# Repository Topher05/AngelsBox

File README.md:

# AngelsBox Leverless Controller

A custom-designed leverless controller for fighting games, inspired by the Flatbox project. This project includes PCB designs created in KiCad and 3D models designed in Fusion 360. Keyboard part footprints from external repositories are utilized for precision and compatibility.

## Features

- **Custom PCB Design**: Designed using KiCad, tailored for leverless controller configurations.
- **3D Models**: Created in Fusion 360 for the case and structural components.
- **Keyboard Compatibility**: Leveraging community-driven footprints for key switches and other keyboard-related parts.
- **Fighting Game Optimized**: Designed with ergonomics and precision in mind for competitive play.
- **Firmware**: Uses [GP2040-CE](https://gp2040-ce.info/web-configurator/) for firmware configuration and setup.

## Contents

1. **PCB Design**:
   - KiCad project files for the controller PCB.
   - Schematic and layout files.
   - Gerber files ready for manufacturing.

2. **3D Models**:
   - Fusion 360 files and exported STL models.
   - Case and structural parts for assembly.

3. **Documentation**:
   - Build instructions and assembly tips.
   - Information about external repositories used for keyboard footprints.

## Requirements

- **KiCad**: For viewing and editing PCB design files.
- **Fusion 360**: For modifying or inspecting the 3D models.
- **3D Printer**: To print the case and other structural parts.
- **PCB Manufacturer**: To fabricate the PCB using the provided Gerber files.
- **Firmware Configurator**: Access [GP2040-CE Web Configurator](https://gp2040-ce.info/web-configurator/) for firmware setup.

## Setup and Assembly

1. **PCB Fabrication**:
   - Send the provided Gerber files to your preferred PCB manufacturer.

2. **3D Printing**:
   - Print the STL files using a 3D printer.
   - Ensure proper filament material based on desired durability and aesthetics.

3. **Assembly**:
   - Solder components onto the fabricated PCB.
   - Assemble the 3D-printed case and secure the PCB inside.
   - Install key switches and other hardware components.

4. **Firmware Configuration**:
   - Use the [GP2040-CE Web Configurator](https://gp2040-ce.info/web-configurator/) to configure the firmware for your controller.

5. **Testing**:
   - Connect the controller to a compatible device.
   - Verify inputs and functionality through fighting game or test software.

## Contributions

This project is open for contributions! If you have improvements or suggestions, feel free to submit pull requests or create issues.

## Acknowledgments

- Thanks to the creators of the Flatbox project for inspiration.
- Gratitude to the contributors of open-source keyboard footprint repositories.

## License

This project is licensed under [MIT License](LICENSE).

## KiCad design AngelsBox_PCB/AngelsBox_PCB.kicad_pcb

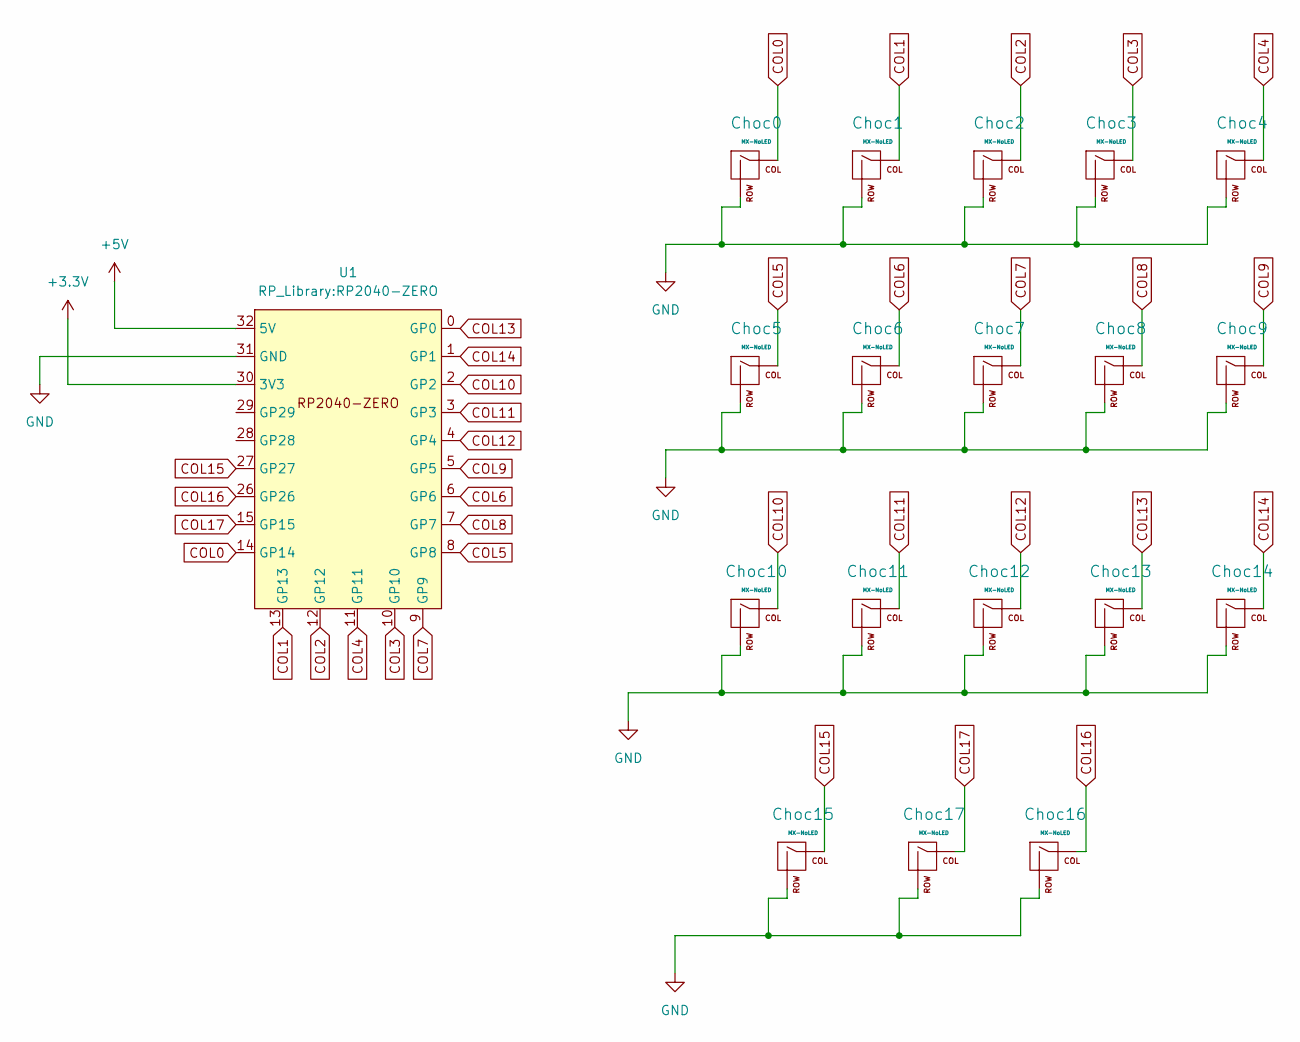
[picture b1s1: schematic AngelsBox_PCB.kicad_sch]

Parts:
Choc0, Choc1, Choc2, Choc3, Choc4, Choc5, Choc6, Choc7, Choc8, Choc9, Choc10, Choc11, Choc12, Choc13, Choc14: MX-NoLED; Kailh_Choc_Hotswap-CircleDesign
Choc15, Choc16, Choc17: MX-NoLED; KailhChoc-1U-Hotswap
U1: RP2040-ZERO

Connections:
+3.3V: U1.30 (3V3)
+5V: U1.32 (5V)
COL0: Choc0.1 (COL), U1.14 (GP14)
COL1: Choc1.1 (COL), U1.13 (GP13)
COL2: Choc2.1 (COL), U1.12 (GP12)
COL3: Choc3.1 (COL), U1.10 (GP10)
COL4: Choc4.1 (COL), U1.11 (GP11)
COL5: Choc5.1 (COL), U1.8 (GP8)
COL6: Choc6.1 (COL), U1.6 (GP6)
COL7: Choc7.1 (COL), U1.9 (GP9)
COL8: Choc8.1 (COL), U1.7 (GP7)
COL9: Choc9.1 (COL), U1.5 (GP5)
COL10: Choc10.1 (COL), U1.2 (GP2)
COL11: Choc11.1 (COL), U1.3 (GP3)
COL12: Choc12.1 (COL), U1.4 (GP4)
COL13: Choc13.1 (COL), U1.0 (GP0)
COL14: Choc14.1 (COL), U1.1 (GP1)
COL15: Choc15.1 (COL), U1.27 (GP27)
COL16: Choc16.1 (COL), U1.26 (GP26)
COL17: Choc17.1 (COL), U1.15 (GP15)
GND: Choc0.2 (ROW), Choc1.2 (ROW), Choc2.2 (ROW), Choc3.2 (ROW), Choc4.2 (ROW), Choc5.2 (ROW), Choc6.2 (ROW), Choc7.2 (ROW), Choc8.2 (ROW), Choc9.2 (ROW), Choc10.2 (ROW), Choc11.2 (ROW), Choc12.2 (ROW), Choc13.2 (ROW), Choc14.2 (ROW), Choc15.2 (ROW), Choc16.2 (ROW), Choc17.2 (ROW), U1.31 (GND)

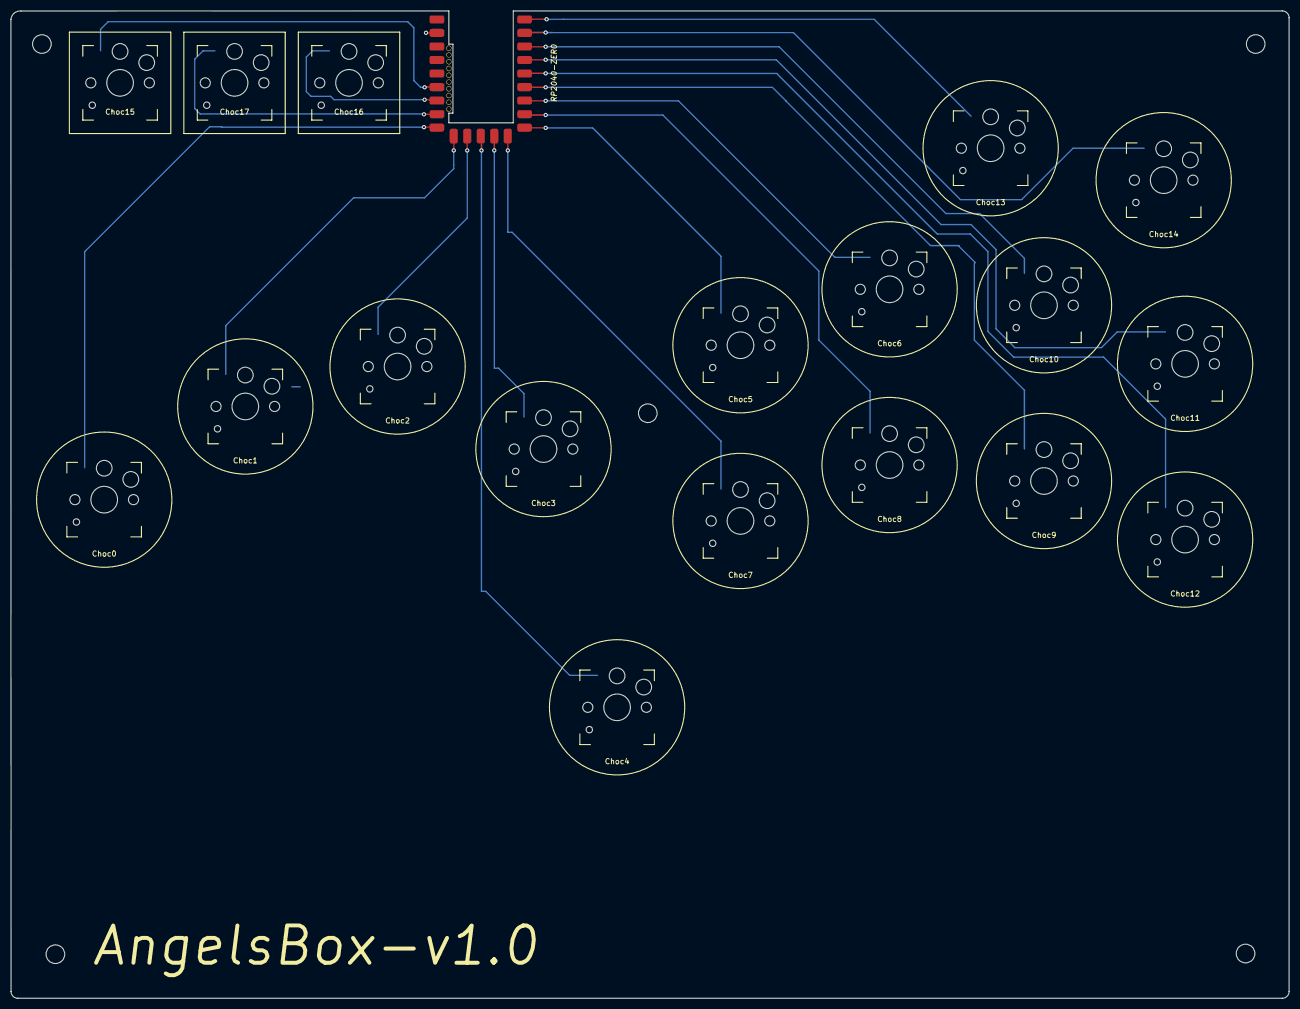
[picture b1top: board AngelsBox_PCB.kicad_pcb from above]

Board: 2 copper layers, 240.1 x 185.4 mm, 19 parts (0 on the bottom side), 19 nets.

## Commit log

2023-08-29 Add submodules
2023-08-29 test
2023-08-29 Adding Libraries
2023-08-31 Foot print for rp2040-zero
2023-09-01 RP2040-Zero Symbol
2023-09-02 First Schematic
2023-09-04 first pcb commit
2023-09-06 Adding hotswap sockets
2024-03-05 Version 1.0 Adds first completed pcb. Adds Gerber files for pcb. Adds 3d stl models for the pcb and first version of keycaps.
2024-05-28 Adding small updates and a dome key cap
2024-10-22 small change to the foot prints for the key switches to support choc v1 and v2
